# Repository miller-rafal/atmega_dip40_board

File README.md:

A reiteration of my previous MCU board project. This board is compatible with
the following ATMega PDIP-40 microcontrollers:
* 164A/PA
* 324A/PA
* 644A/PA
* 1284/P

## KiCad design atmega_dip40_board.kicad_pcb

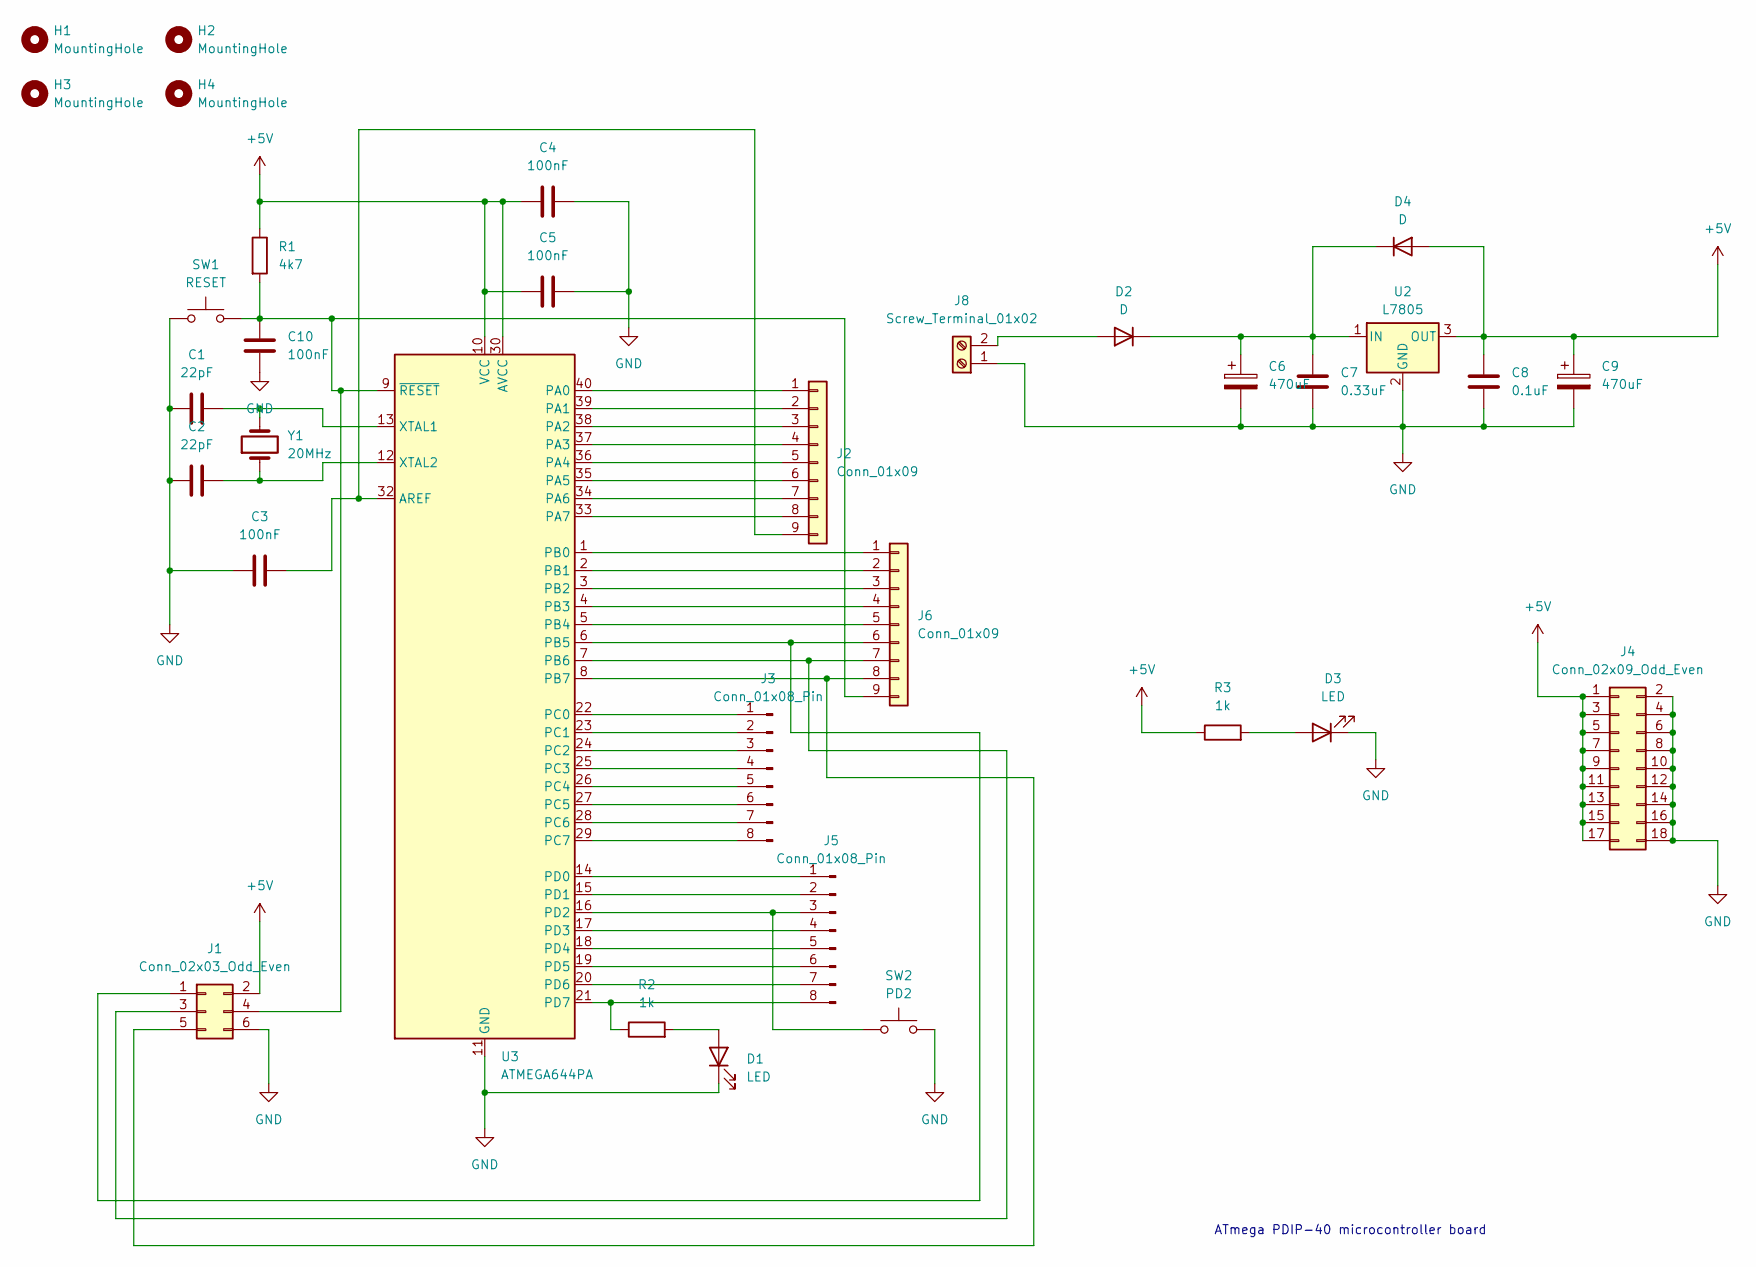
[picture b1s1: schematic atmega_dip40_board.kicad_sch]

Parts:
C1, C2: 22pF; C_Disc_D6.0mm_W2.5mm_P5.00mm
C3, C4, C5, C10: 100nF; C_Disc_D6.0mm_W2.5mm_P5.00mm
C6, C9: 470uF; CP_Radial_D10.0mm_P5.00mm
C7: 0.33uF; C_Disc_D6.0mm_W2.5mm_P5.00mm
C8: 0.1uF; C_Disc_D6.0mm_W2.5mm_P5.00mm
D1, D3: LED; LED_D5.0mm
D2, D4: D; D_DO-41_SOD81_P7.62mm_Horizontal
H1, H2, H3, H4: MountingHole; MountingHole_2.5mm
J1: Conn_02x03_Odd_Even; PinHeader_2x03_P2.54mm_Vertical
J2, J6: Conn_01x09; PinHeader_1x09_P2.54mm_Vertical
J3, J5: Conn_01x08_Pin; PinHeader_1x08_P2.54mm_Vertical
J4: Conn_02x09_Odd_Even; PinHeader_2x09_P2.54mm_Vertical
J8: Screw_Terminal_01x02; TerminalBlock_bornier-2_P5.08mm
R1: 4k7; R_Axial_DIN0207_L6.3mm_D2.5mm_P10.16mm_Horizontal
R2, R3: 1k; R_Axial_DIN0207_L6.3mm_D2.5mm_P10.16mm_Horizontal
SW1: RESET; SW_PUSH_6mm
SW2: PD2; SW_PUSH_6mm
U2: L7805; TO-220-3_Vertical
U3: ATMEGA644PA; DIP-40_W15.24mm
Y1: 20MHz; Crystal_HC49-U_Vertical

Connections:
+5V: C4.2, C5.2, C8.1, C9.1, D4.2 (A), J1.2, J4.1, J4.3, J4.5, J4.7, J4.9, J4.11, J4.13, J4.15, J4.17, R1.1, R3.1, U2.3 (OUT), U3.10 (VCC), U3.30 (AVCC)
GND: C1.2, C2.2, C3.2, C4.1, C5.1, C6.2, C7.2, C8.2, C9.2, C10.2, D1.1 (K), D3.1 (K), J1.6, J4.2, J4.4, J4.6, J4.8, J4.10, J4.12, J4.14, J4.16, J4.18, J8.1, SW1.1, SW2.2, U2.2 (GND), U3.11 (GND), U3.31 (GND)
unnamed: D1.2 (A), R2.2
unnamed: D2.2 (A), J8.2
unnamed: C6.1, C7.1, D2.1 (K), D4.1 (K), U2.1 (IN)
unnamed: D3.2 (A), R3.2
unnamed: J1.1, J6.6, U3.6 (PB5)
unnamed: J1.3, J6.7, U3.7 (PB6)
unnamed: C10.1, J1.4, J6.9, R1.2, SW1.2, U3.9 (~RESET)
unnamed: J1.5, J6.8, U3.8 (PB7)
unnamed: J2.1, U3.40 (PA0)
unnamed: J2.2, U3.39 (PA1)
unnamed: J2.3, U3.38 (PA2)
unnamed: J2.4, U3.37 (PA3)
unnamed: J2.5, U3.36 (PA4)
unnamed: J2.6, U3.35 (PA5)
unnamed: J2.7, U3.34 (PA6)
unnamed: J2.8, U3.33 (PA7)
unnamed: C3.1, J2.9, U3.32 (AREF)
unnamed: J3.1, U3.22 (PC0)
unnamed: J3.2, U3.23 (PC1)
unnamed: J3.3, U3.24 (PC2)
unnamed: J3.4, U3.25 (PC3)
unnamed: J3.5, U3.26 (PC4)
unnamed: J3.6, U3.27 (PC5)
unnamed: J3.7, U3.28 (PC6)
unnamed: J3.8, U3.29 (PC7)
unnamed: J5.1, U3.14 (PD0)
unnamed: J5.2, U3.15 (PD1)
unnamed: J5.3, SW2.1, U3.16 (PD2)
unnamed: J5.4, U3.17 (PD3)
unnamed: J5.5, U3.18 (PD4)
unnamed: J5.6, U3.19 (PD5)
unnamed: J5.7, U3.20 (PD6)
unnamed: J5.8, R2.1, U3.21 (PD7)
unnamed: J6.1, U3.1 (PB0)
unnamed: J6.2, U3.2 (PB1)
unnamed: J6.3, U3.3 (PB2)
unnamed: J6.4, U3.4 (PB3)
unnamed: J6.5, U3.5 (PB4)
unnamed: C1.1, U3.13 (XTAL1), Y1.2
unnamed: C2.1, U3.12 (XTAL2), Y1.1

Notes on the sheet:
ATmega PDIP-40 microcontroller board

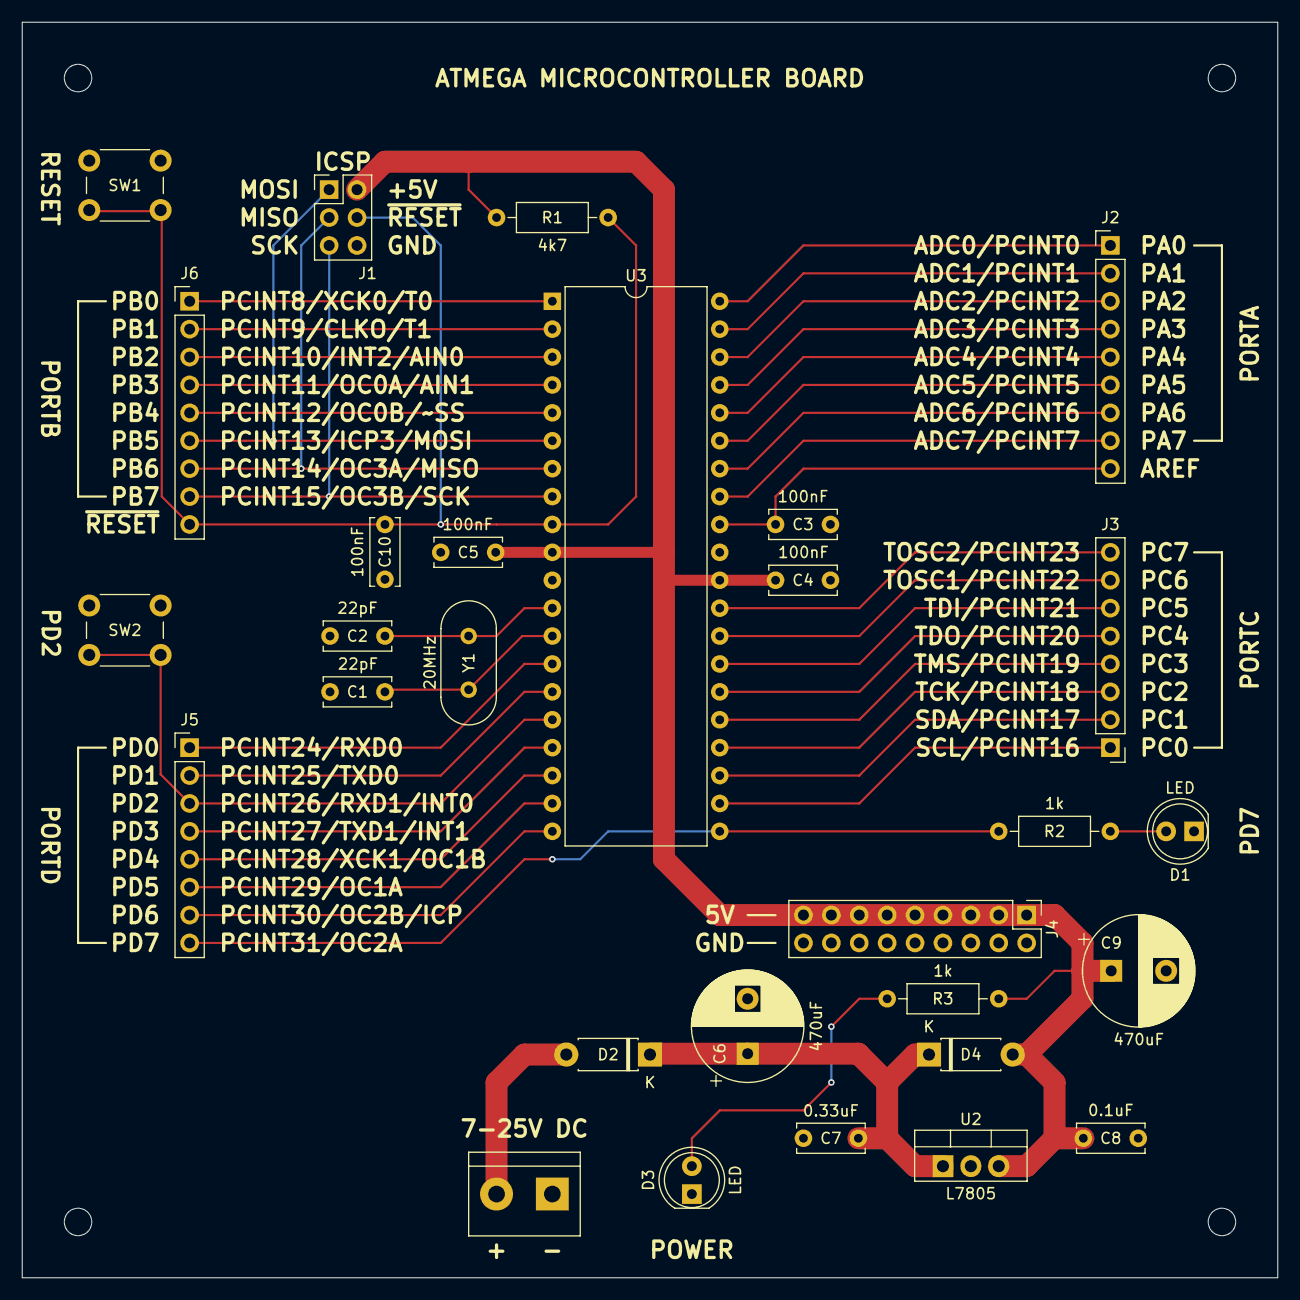
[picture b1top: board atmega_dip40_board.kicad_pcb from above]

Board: 2 copper layers, 114.3 x 114.3 mm, 33 parts (0 on the bottom side), 42 nets.
